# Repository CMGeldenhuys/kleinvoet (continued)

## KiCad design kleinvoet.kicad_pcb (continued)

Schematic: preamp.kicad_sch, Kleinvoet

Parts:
C1601: 18n; C_0805_2012Metric; MPN GRM21B5C1H183JA01K
C1602: PH/DNP; R_0402_1005Metric; not fitted
C1603, C1604: 2.7n; C_0402_1005Metric; MPN GRM1555C1H272GE01D
C1605: 1u; C_0402_1005Metric; MPN C0402C105K9PACTU
C1606, C1607: 220p; C_0402_1005Metric; MPN GRT1555C1H221FA02D
CB1601, CB1602: 100n; C_0402_1005Metric; MPN C0402C104K8PACTU
R1601, R1602: 270; R_0402_1005Metric; MPN RT0402FRE07270RL
R1603, R1604: 330E; R_0402_1005Metric; MPN RT0402FRE07330RL
R1605, R1606: 1k; R_0402_1005Metric; MPN RT0402FRE071KL
R1607, R1608: 15E; R_0402_1005Metric; MPN RT0402FRE0715RL
U1701: THS4551xRGT; VQFN-16-1EP_3x3mm_P0.5mm_EP1.68x1.68mm_ThermalVias; MPN THS4551IRGTR

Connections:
+1V8: CB1602.1, R1601.2, U1701.9 (VOCM); also elsewhere on the board
+3.3V_SENSOR: C1605.2, CB1601.1, U1701.5 (VS+), U1701.6 (VS+), U1701.7 (VS+), U1701.8 (VS+), U1701.12 (~PD); also elsewhere on the board
/Sensor_board/Preamplifier/FB: C1603.1, U1701.4 (FB+)
/Sensor_board/Preamplifier/FDA_IN: C1602.2, C1604.2, R1604.1, U1701.2 (IN+)
/Sensor_board/Preamplifier/FDA_~IN: C1602.1, C1603.2, R1603.1, U1701.3 (IN-)
/Sensor_board/Preamplifier/OUT: R1607.2, U1701.10 (OUT+)
/Sensor_board/Preamplifier/SIG_N: R1606.1, R1608.1; also elsewhere on the board
/Sensor_board/Preamplifier/SIG_P: R1605.1, R1607.1; also elsewhere on the board
/Sensor_board/Preamplifier/~FB: C1604.1, U1701.1 (FB-)
/Sensor_board/Preamplifier/~OUT: R1608.2, U1701.11 (OUT-)
/Sensor_board/SUM_OUT_P: R1602.2; also elsewhere on the board
GND_SENSOR: C1605.1, C1606.1, C1607.1, CB1601.2, CB1602.2, U1701.13 (VS-), U1701.14 (VS-), U1701.15 (VS-), U1701.16 (VS-), U1701.17 (EP); also elsewhere on the board
unnamed: C1601.1, C1606.2, R1601.1, R1603.2, R1605.2
unnamed: C1601.2, C1607.2, R1602.1, R1604.2, R1606.2

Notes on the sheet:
See sheet "/ADC_Interface/ADC_AA_1" for more information.
CONNECTED INTERNALLY

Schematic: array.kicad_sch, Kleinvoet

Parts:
C1401, C1402, C1501, C1503, C1505, C1506, C1507, C1508: 1u; C_0402_1005Metric; MPN C0402C105K9PACTU
CB1401, CB1402, CB1403, CB1404, CB1405, CB1406, CB1407, CB1408: 100n; C_0402_1005Metric; MPN C0402C104K8PACTU
MK1401, MK1402, MK1403, MK1404, MK1405, MK1406, MK1407, MK1408: MIC_ICS_40300; MEMS_Mic_ICS-40300; MPN ICS-40300

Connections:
+1V8: C1401.1, C1402.1, C1501.1, C1503.1, C1505.1, C1506.1, C1507.1, C1508.1, CB1401.1, CB1402.1, CB1403.1, CB1404.1, CB1405.1, CB1406.1, CB1407.1, CB1408.1, MK1401.5 (VDD), MK1402.5 (VDD), MK1403.5 (VDD), MK1404.5 (VDD), MK1405.5 (VDD), MK1406.5 (VDD), MK1407.5 (VDD), MK1408.5 (VDD); also elsewhere on the board
/Sensor_board/Buffer/IN0: MK1404.1 (OUTPUT); also elsewhere on the board
/Sensor_board/Buffer/IN1: MK1406.1 (OUTPUT); also elsewhere on the board
/Sensor_board/Buffer/IN2: MK1402.1 (OUTPUT); also elsewhere on the board
/Sensor_board/Buffer/IN3: MK1408.1 (OUTPUT); also elsewhere on the board
/Sensor_board/Buffer/IN4: MK1403.1 (OUTPUT); also elsewhere on the board
/Sensor_board/Buffer/IN5: MK1405.1 (OUTPUT); also elsewhere on the board
/Sensor_board/Buffer/IN6: MK1401.1 (OUTPUT); also elsewhere on the board
/Sensor_board/Buffer/IN7: MK1407.1 (OUTPUT); also elsewhere on the board
GND_SENSOR: C1401.2, C1402.2, C1501.2, C1503.2, C1505.2, C1506.2, C1507.2, C1508.2, CB1401.2, CB1402.2, CB1403.2, CB1404.2, CB1405.2, CB1406.2, CB1407.2, CB1408.2, MK1401.2 (GND), MK1401.3 (GND), MK1401.4 (GND), MK1401.6 (GND), MK1402.2 (GND), MK1402.3 (GND), MK1402.4 (GND), MK1402.6 (GND), MK1403.2 (GND), MK1403.3 (GND), MK1403.4 (GND), MK1403.6 (GND), MK1404.2 (GND), MK1404.3 (GND), MK1404.4 (GND), MK1404.6 (GND), MK1405.2 (GND), MK1405.3 (GND), MK1405.4 (GND), MK1405.6 (GND), MK1406.2 (GND), MK1406.3 (GND), MK1406.4 (GND), MK1406.6 (GND), MK1407.2 (GND), MK1407.3 (GND), MK1407.4 (GND), MK1407.6 (GND), MK1408.2 (GND), MK1408.3 (GND), MK1408.4 (GND), MK1408.6 (GND); also elsewhere on the board

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
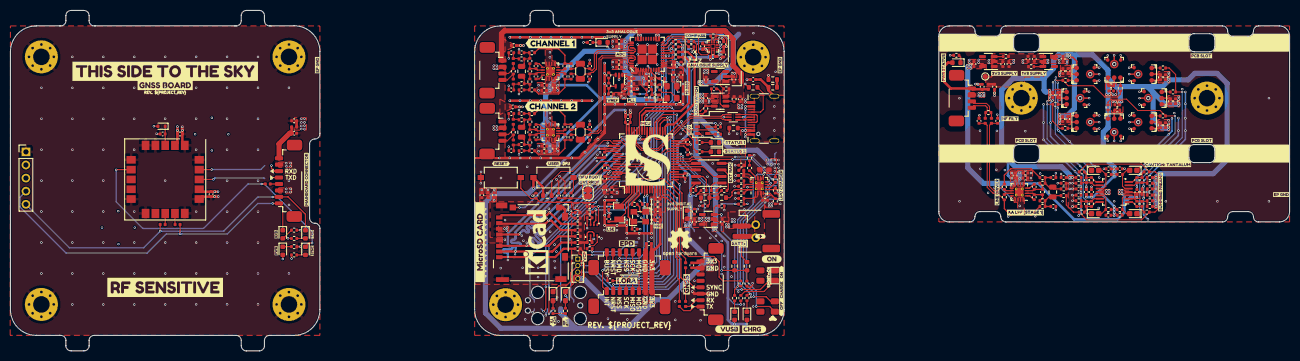
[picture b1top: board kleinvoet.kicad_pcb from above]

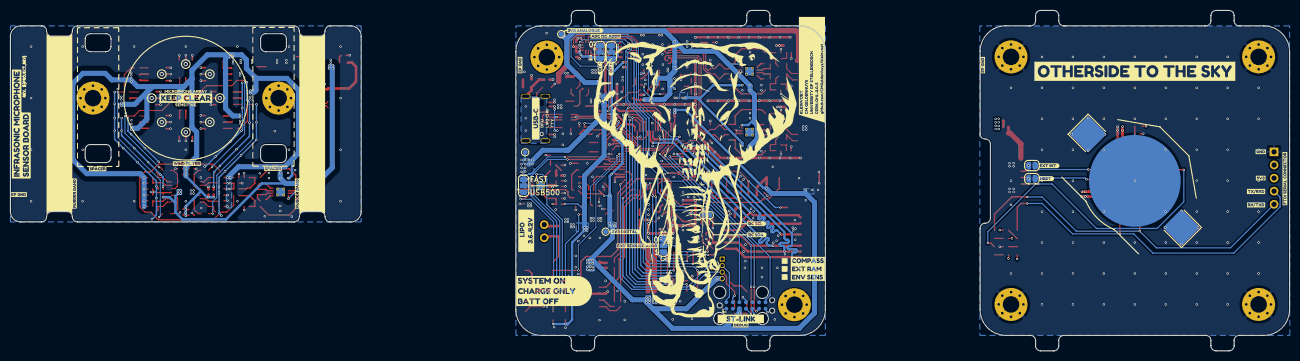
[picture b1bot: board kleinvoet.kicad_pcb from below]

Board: 4 copper layers, 248.0 x 66.0 mm, 500 parts (50 on the bottom side), 219 nets.

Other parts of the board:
303: Tab
B1, B2, B3: Board
T103, T104, T105, T106, T107, T109, T201, T203, T205, T206, T208, T209, T306, T307, T309, T311: Tab
kibuzzard-64FAE4D6: G***; kibuzzard-64FAE4D6
kibuzzard-64FAE5CE: G***; kibuzzard-64FAE5CE
kibuzzard-64FAE5F7: G***; kibuzzard-64FAE5F7
kibuzzard-64FAE496: G***; kibuzzard-64FAE496
kibuzzard-64FAEA81: G***; kibuzzard-64FAEA81
kibuzzard-64FAEAB3: G***; kibuzzard-64FAEAB3
kibuzzard-644FCAF5: G***; kibuzzard-644FCAF5
kibuzzard-644FCBD8: G***; kibuzzard-644FCBD8
kibuzzard-644FCBE4: G***; kibuzzard-644FCBE4
kibuzzard-644FCC8B: G***; kibuzzard-644FCC8B
kibuzzard-644FCC84: G***; kibuzzard-644FCC84
kibuzzard-644FCD41: G***; kibuzzard-644FCD41
kibuzzard-644FCD80: G***; kibuzzard-644FCD80
kibuzzard-644FCF30: G***; kibuzzard-644FCF30
kibuzzard-644FCFAB: G***; kibuzzard-644FCFAB
kibuzzard-644FD0BF: G***; kibuzzard-644FD0BF
kibuzzard-644FD0EC: G***; kibuzzard-644FD0EC
kibuzzard-644FD1C9: G***; kibuzzard-644FD1C9
kibuzzard-644FD1E4: G***; kibuzzard-644FD1E4
kibuzzard-644FD2E5: G***; kibuzzard-644FD2E5
kibuzzard-644FD9A3: G***; kibuzzard-644FD9A3
kibuzzard-644FD9EF: G***; kibuzzard-644FD9EF
kibuzzard-644FD32B: G***; kibuzzard-644FD32B
kibuzzard-644FD84A: G***; kibuzzard-644FD84A
kibuzzard-644FD97C: G***; kibuzzard-644FD97C
kibuzzard-644FD164: G***; kibuzzard-644FD164
kibuzzard-644FD811: G***; kibuzzard-644FD811
kibuzzard-644FD964: G***; kibuzzard-644FD964
kibuzzard-644FDA17: G***; kibuzzard-644FDA17
kibuzzard-644FDE8C: G***; kibuzzard-644FDE8C
kibuzzard-644FDEA0: G***; kibuzzard-644FDEA0
kibuzzard-644FDEAE: G***; kibuzzard-644FDEAE
kibuzzard-644FDEBE: G***; kibuzzard-644FDEBE
kibuzzard-644FDED0: G***; kibuzzard-644FDED0
kibuzzard-644FDEDF: G***; kibuzzard-644FDEDF
kibuzzard-644FDEEE: G***; kibuzzard-644FDEEE
kibuzzard-644FDF3B: G***; kibuzzard-644FDF3B
kibuzzard-644FDF29: G***; kibuzzard-644FDF29
kibuzzard-644FDF72: G***; kibuzzard-644FDF72
kibuzzard-644FDF97: G***; kibuzzard-644FDF97
kibuzzard-644FDFE0: G***; kibuzzard-644FDFE0
kibuzzard-644FDFE9: G***; kibuzzard-644FDFE9
kibuzzard-644FE0B0: G***; kibuzzard-644FE0B0
kibuzzard-644FE0C7: G***; kibuzzard-644FE0C7
kibuzzard-644FE0D3: G***; kibuzzard-644FE0D3
kibuzzard-644FE0E6: G***; kibuzzard-644FE0E6
kibuzzard-644FE0FE: G***; kibuzzard-644FE0FE
kibuzzard-644FE022: G***; kibuzzard-644FE022
kibuzzard-644FE057: G***; kibuzzard-644FE057
kibuzzard-644FEC52: G***; kibuzzard-644FEC52
kibuzzard-644FEC78: G***; kibuzzard-644FEC78
kibuzzard-693A62A4: G***; kibuzzard-693A62A4
kibuzzard-6937DD7F: G***; kibuzzard-6937DD7F
kibuzzard-6937DDBE: G***; kibuzzard-6937DDBE
kibuzzard-6937DDCD: G***; kibuzzard-6937DDCD
kibuzzard-6937DDE0: G***; kibuzzard-6937DDE0
kibuzzard-6937E0C6: G***; kibuzzard-6937E0C6
kibuzzard-6937E02E: G***; kibuzzard-6937E02E
kibuzzard-6937E9BB: G***; kibuzzard-6937E9BB
kibuzzard-6937E996: G***; kibuzzard-6937E996
kibuzzard-6937EA9A: G***; kibuzzard-6937EA9A
kibuzzard-64588AF5: G***; kibuzzard-64588AF5
kibuzzard-64588B83, kibuzzard-64588B83#2: G***; kibuzzard-64588B83
kibuzzard-64588C0F: G***; kibuzzard-64588C0F
kibuzzard-64588C44: G***; kibuzzard-64588C44
kibuzzard-64588CA5: G***; kibuzzard-64588CA5
kibuzzard-64588D6D: G***; kibuzzard-64588D6D
kibuzzard-64588D28, kibuzzard-64588D28#2, kibuzzard-64588D28#3: G***; kibuzzard-64588D28
kibuzzard-64588D84: G***; kibuzzard-64588D84
kibuzzard-64588F88, kibuzzard-64588F88#2: G***; kibuzzard-64588F88
kibuzzard-64588FFA: G***; kibuzzard-64588FFA
kibuzzard-64589A68: G***; kibuzzard-64589A68
kibuzzard-645890C3: G***; kibuzzard-645890C3
kibuzzard-645890EE: G***; kibuzzard-645890EE
kibuzzard-645891C0: G***; kibuzzard-645891C0
kibuzzard-645891F3: G***; kibuzzard-645891F3
kibuzzard-645892E6, kibuzzard-645892E6#2, kibuzzard-645892E6#3, kibuzzard-645892E6#4, kibuzzard-645892E6#5, kibuzzard-645892E6#6: G***; kibuzzard-645892E6
kibuzzard-6458903B: G***; kibuzzard-6458903B
kibuzzard-6458905C: G***; kibuzzard-6458905C
kibuzzard-6458907D: G***; kibuzzard-6458907D
kibuzzard-6458908B: G***; kibuzzard-6458908B
kibuzzard-6458936C: G***; kibuzzard-6458936C
kibuzzard-6458938C: G***; kibuzzard-6458938C
kibuzzard-64589097: G***; kibuzzard-64589097
kibuzzard-64589363: G***; kibuzzard-64589363

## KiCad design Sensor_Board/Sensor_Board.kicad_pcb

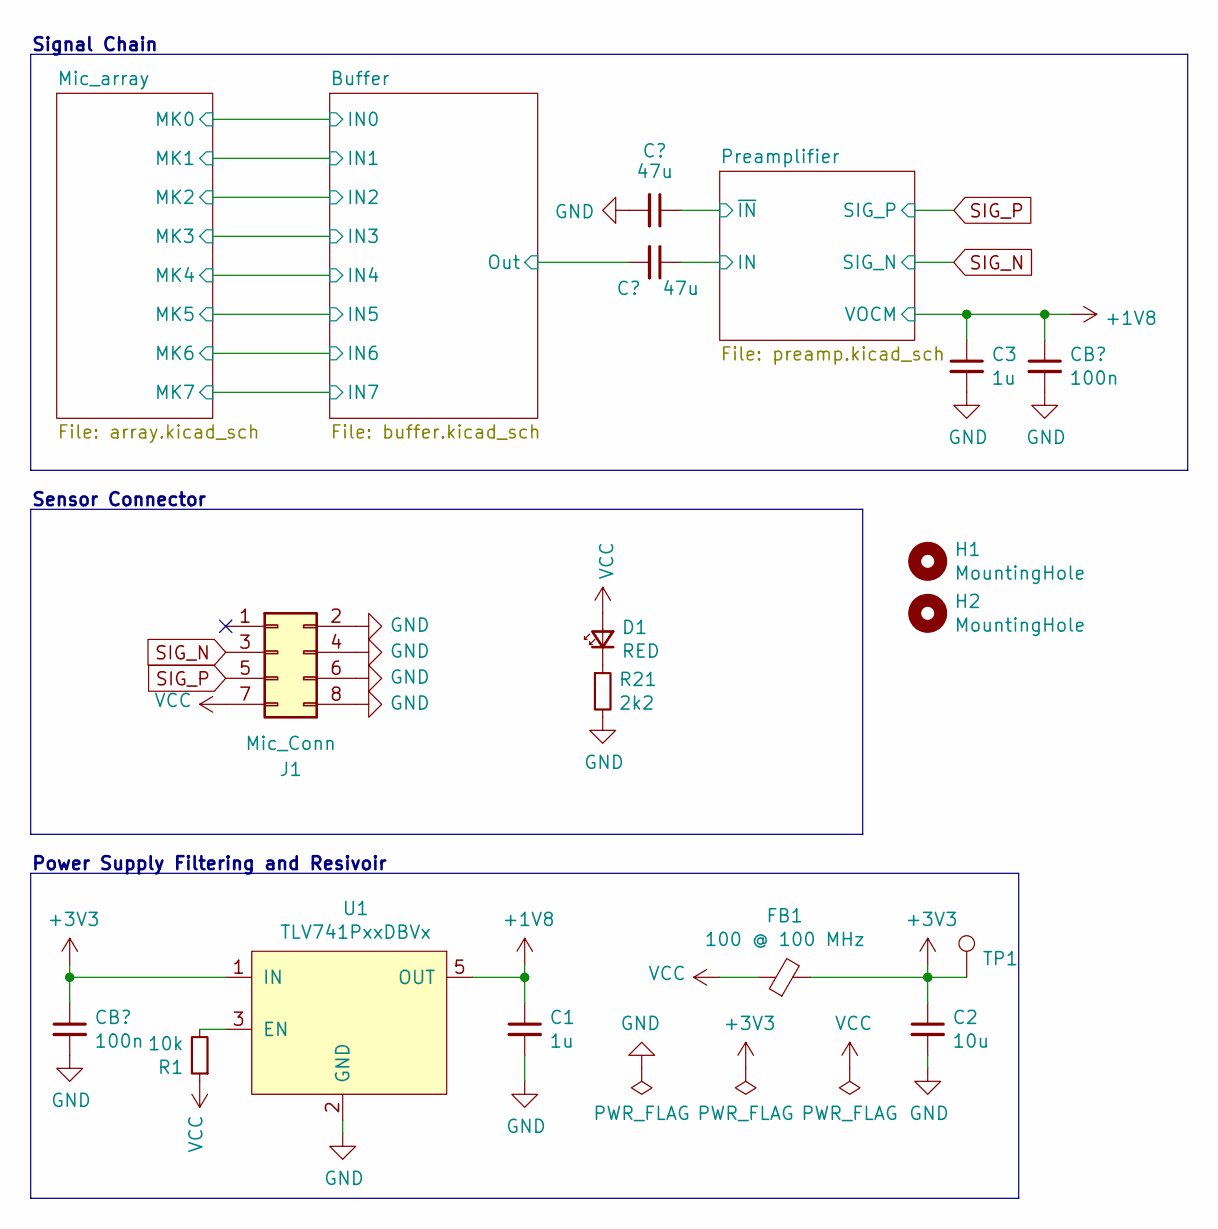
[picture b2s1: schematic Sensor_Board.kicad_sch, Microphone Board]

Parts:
C1, C3: 1u; C_0603_1608Metric_Pad1.08x0.95mm_HandSolder; MPN C0603C105K8RACTU
C2: 10u; C_0805_2012Metric_Pad1.18x1.45mm_HandSolder; MPN C0805C106K9PACTU
C10, C11: 47u; C_1206_3216Metric_Pad1.33x1.80mm_HandSolder; MPN GRM31CR60J107KE39K
CB1, CB3: 100n; C_0603_1608Metric_Pad1.08x0.95mm_HandSolder; MPN C0603C104M5RACTU
D1: RED; LED_0603_1608Metric_Pad1.05x0.95mm_HandSolder; MPN SML-D12U8WT86C
FB1: 100 @ 100 MHz; L_0603_1608Metric_Pad1.05x0.95mm_HandSolder; MPN BLM18EG101TZ1D
H1, H2: MountingHole; MountingHole_3.2mm_M3_Pad_Via
J1: Mic_Conn; TE_7-215079-8; MPN 7-215079-8, 7-215083-8
R1: 10k; R_0603_1608Metric_Pad0.98x0.95mm_HandSolder; MPN RC0603JR-0710KL
R21: 2k2; R_0603_1608Metric_Pad0.98x0.95mm_HandSolder; MPN ERJ-3EKF2201V
TP1: TestPoint; TestPoint_Pad_D1.0mm; MPN ICS-40300
U1: TLV741PxxDBVx; SOT-23-5; MPN TLV74118PDBVR

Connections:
+1V8: C1.1, C3.1, CB3.1, U1.5 (OUT); also elsewhere on the board
+3V3: C2.1, CB1.1, FB1.2, TP1.1, U1.1 (IN); also elsewhere on the board
/Buffer/Out: C11.2; also elsewhere on the board
/Preamplifier/IN: C11.1; also elsewhere on the board
/Preamplifier/~IN: C10.1; also elsewhere on the board
GND: C1.2, C2.2, C3.2, C10.2, CB1.2, CB3.2, J1.2, J1.4, J1.6, J1.8, R21.2, U1.2 (GND); also elsewhere on the board
unnamed: D1.1 (K), R21.1
unnamed: R1.2, U1.3 (EN)
SIG_N: J1.3; also elsewhere on the board
SIG_P: J1.5; also elsewhere on the board
VCC: D1.2 (A), FB1.1, J1.7, R1.1

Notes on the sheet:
Power Supply Filtering and Resivoir
Signal Chain
Sensor Connector

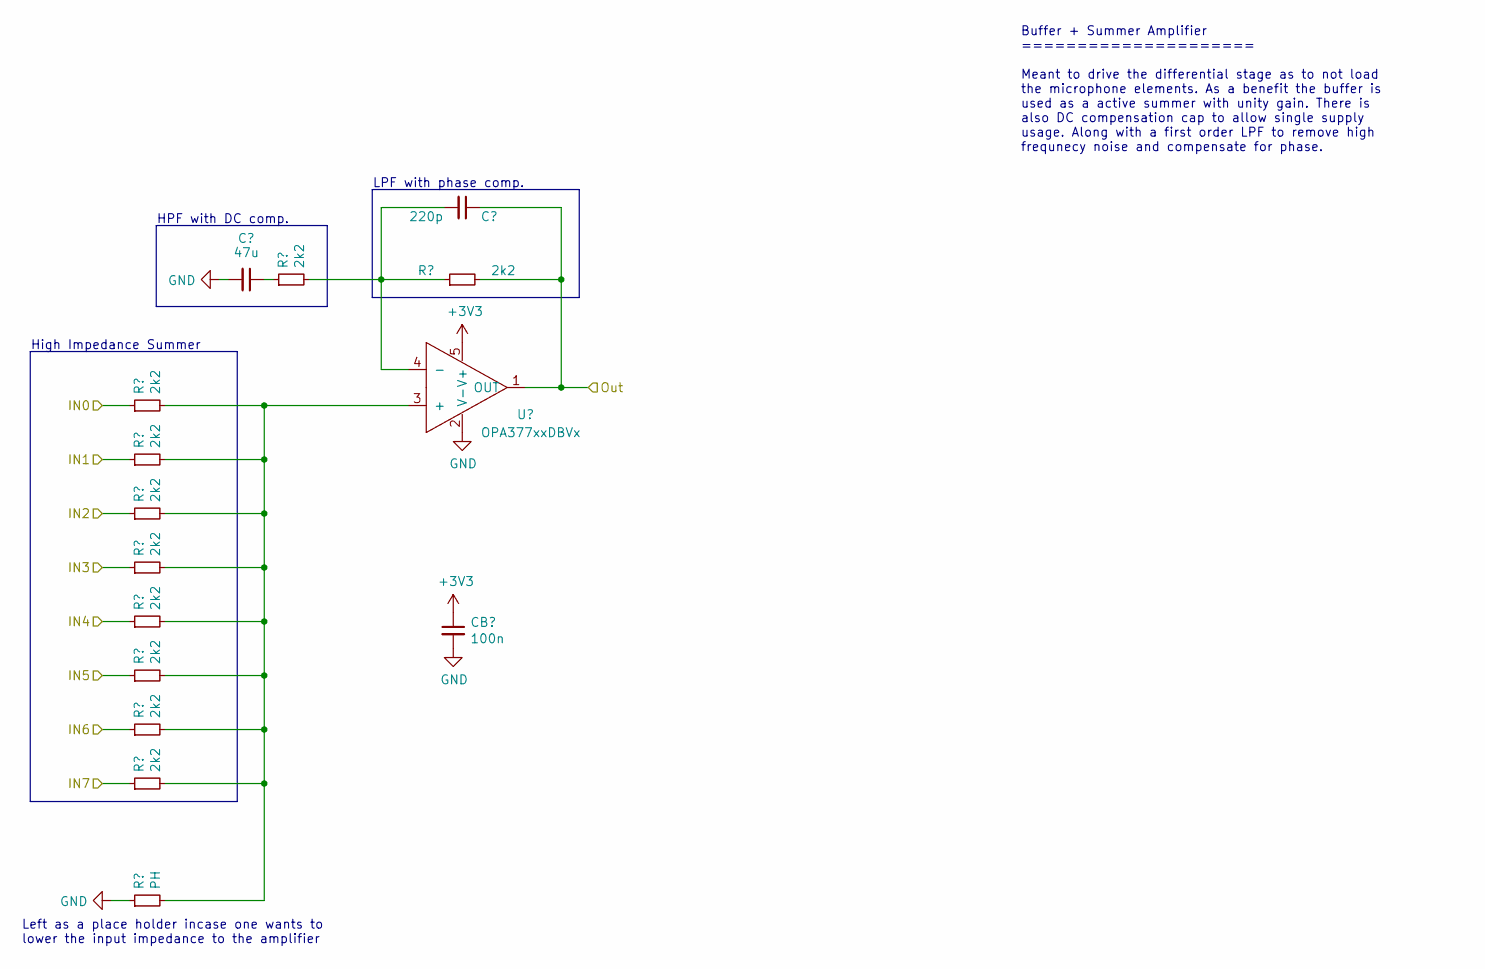
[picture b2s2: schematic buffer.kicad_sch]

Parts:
C4: 47u; C_1206_3216Metric_Pad1.33x1.80mm_HandSolder; MPN GRM31CR60J107KE39K
C5: 220p; C_0603_1608Metric_Pad1.08x0.95mm_HandSolder; MPN C0603C221J5GACTU
CB4: 100n; C_0603_1608Metric_Pad1.08x0.95mm_HandSolder; MPN C0603C104M5RACTU
R2, R3, R4, R5, R6, R7, R8, R9, R11, R12: 2k2; R_0603_1608Metric_Pad0.98x0.95mm_HandSolder; MPN ERJ-3EKF2201V
R10: PH; R_0603_1608Metric_Pad0.98x0.95mm_HandSolder
U2: OPA377xxDBVx; SOT-23-5; MPN OPA377AIDBVR

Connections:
+3V3: CB4.1, U2.5 (V+); also elsewhere on the board
/Buffer/IN0: R2.1; also elsewhere on the board
/Buffer/IN1: R3.1; also elsewhere on the board
/Buffer/IN2: R4.1; also elsewhere on the board
/Buffer/IN3: R5.1; also elsewhere on the board
/Buffer/IN4: R6.1; also elsewhere on the board
/Buffer/IN5: R7.1; also elsewhere on the board
/Buffer/IN6: R8.1; also elsewhere on the board
/Buffer/IN7: R9.1; also elsewhere on the board
/Buffer/Out: C5.1, R12.2, U2.1 (OUT); also elsewhere on the board
GND: C4.2, CB4.2, R10.1, U2.2 (V-); also elsewhere on the board
unnamed: C4.1, R11.1
unnamed: C5.2, R11.2, R12.1, U2.4 (-)
unnamed: R2.2, R3.2, R4.2, R5.2, R6.2, R7.2, R8.2, R9.2, R10.2, U2.3 (+)

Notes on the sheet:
Buffer + Summer Amplifier ===================== Meant to drive the differential stage as to not load the microphone elements. As a benefit the buffer is used as a active summer with unity gain. There is also DC compensation cap to allow single supply usage. Along with a first order LPF to remove hi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
HPF with DC comp.
High Impedance Summer
LPF with phase comp.
Left as a place holder incase one wants to lower the input impedance to the amplifier

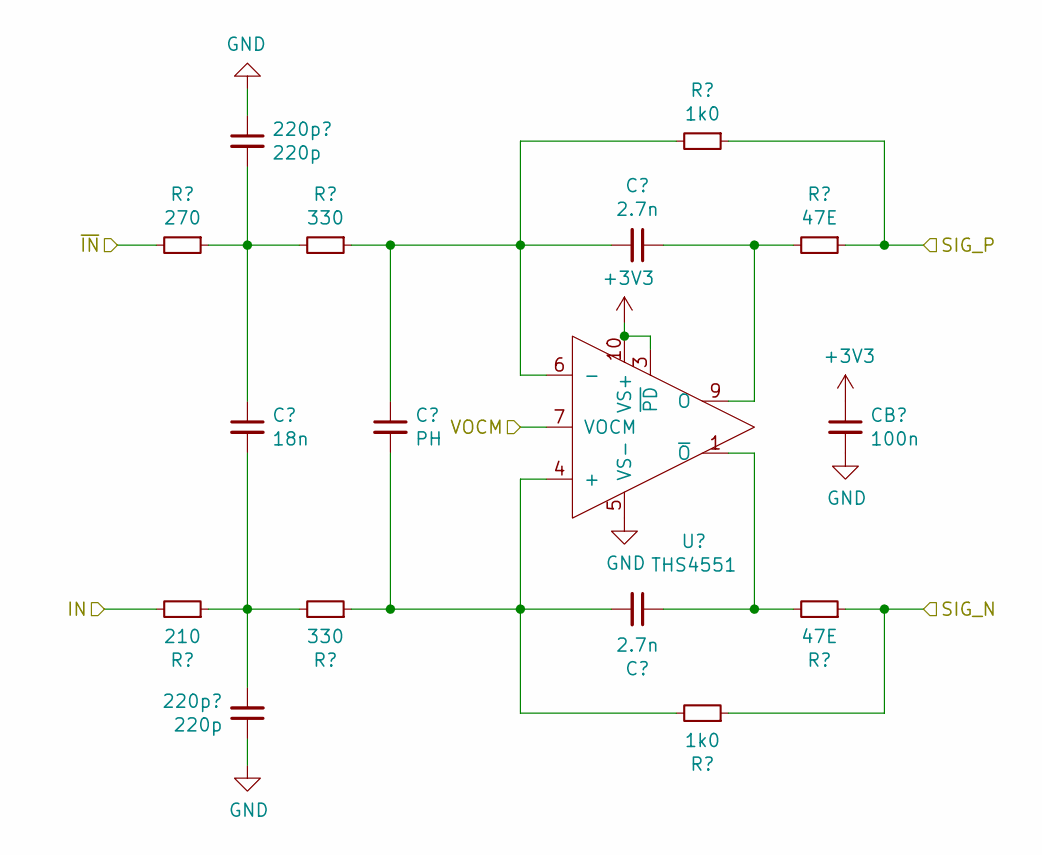
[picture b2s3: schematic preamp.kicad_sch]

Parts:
C6: 18n; C_0603_1608Metric_Pad1.08x0.95mm_HandSolder; MPN CC0603JRX7R8BB183
C7: PH; R_0603_1608Metric_Pad0.98x0.95mm_HandSolder
C8, C9: 2.7n; C_0603_1608Metric_Pad1.08x0.95mm_HandSolder; MPN CC0603JRX7R9BB272
C12, C13: 220p; C_0603_1608Metric_Pad1.08x0.95mm_HandSolder; MPN C0603C221J5GACTU
CB5: 100n; C_0603_1608Metric_Pad1.08x0.95mm_HandSolder; MPN C0603C104M5RACTU
R13: 270; R_0603_1608Metric_Pad0.98x0.95mm_HandSolder; MPN ERJ-3EKF2700V
R14: 210; R_0603_1608Metric_Pad0.98x0.95mm_HandSolder; MPN ERJ-3EKF2100V
R15, R16: 330; R_0603_1608Metric_Pad0.98x0.95mm_HandSolder; MPN ERJ-3EKF3300V
R17, R18: 1k0; R_0603_1608Metric_Pad0.98x0.95mm_HandSolder; MPN ERJ-3EKF1001V
R19, R20: 47E; R_0603_1608Metric_Pad0.98x0.95mm_HandSolder; MPN ERJ-3EKF47R0V
U3: THS4551; WQFN-10_RUN; MPN THS4551IRUNR

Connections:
+1V8: U3.7 (VOCM); also elsewhere on the board
+3V3: CB5.1, U3.3 (~PD), U3.10 (VS+); also elsewhere on the board
/Preamplifier/IN: R14.2; also elsewhere on the board
/Preamplifier/~IN: R13.2; also elsewhere on the board
GND: C12.1, C13.1, CB5.2, U3.5 (VS-); also elsewhere on the board
unnamed: C7.1, C8.2, R15.1, R17.2, U3.6 (-)
unnamed: C7.2, C9.2, R16.1, R18.2, U3.4 (+)
unnamed: C8.1, R19.2, U3.9 (O)
unnamed: C9.1, R20.2, U3.1 (~O)
unnamed: C6.1, C12.2, R13.1, R15.2
unnamed: C6.2, C13.2, R14.1, R16.2
SIG_N: R18.1, R20.1; also elsewhere on the board
SIG_P: R17.1, R19.1; also elsewhere on the board

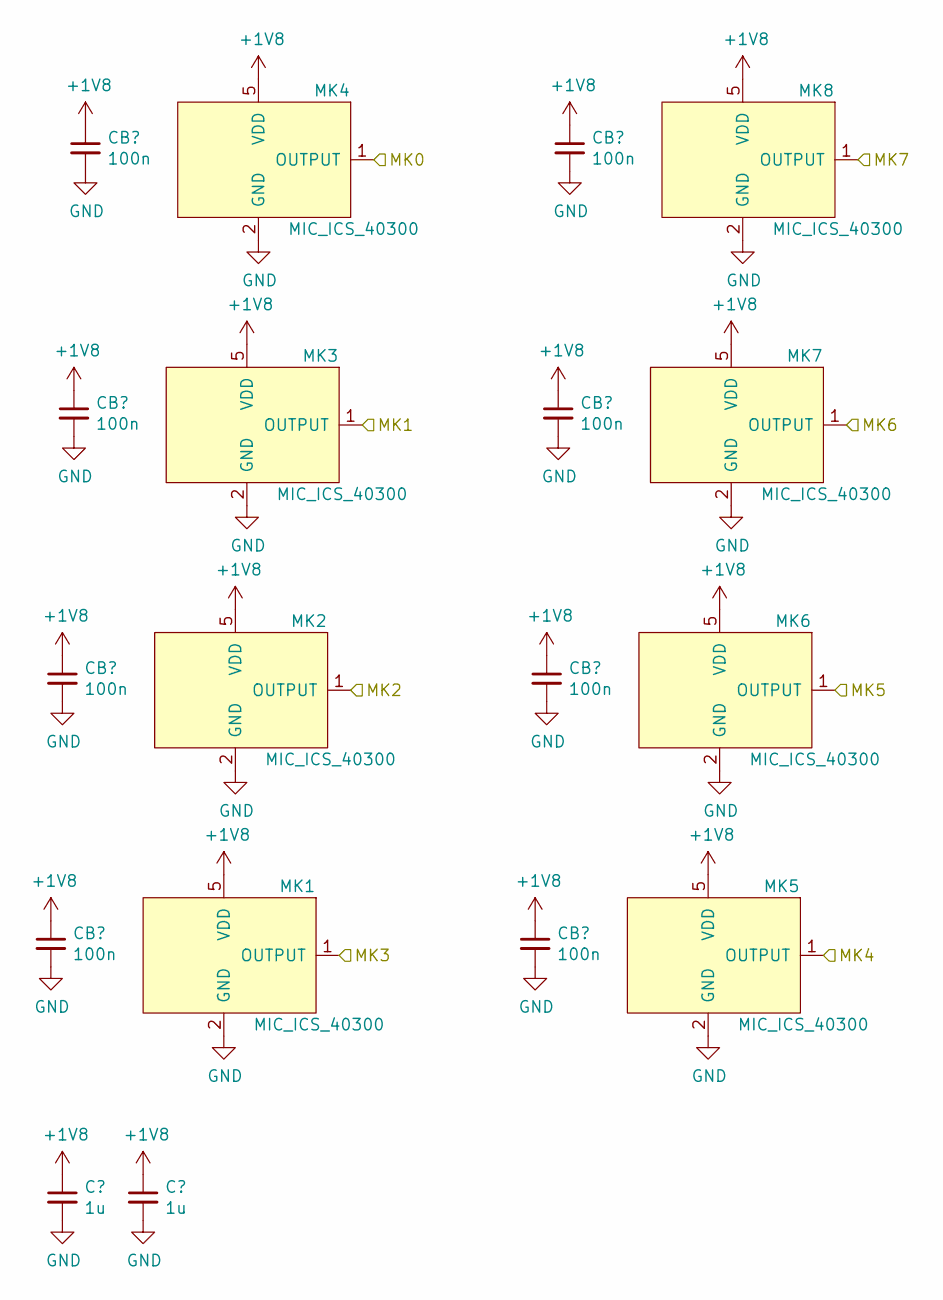
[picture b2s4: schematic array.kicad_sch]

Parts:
C14, C15: 1u; C_0603_1608Metric_Pad1.08x0.95mm_HandSolder; MPN C0603C105K8RACTU
CB6, CB7, CB8, CB9, CB10, CB11, CB12, CB13: 100n; C_0603_1608Metric_Pad1.08x0.95mm_HandSolder; MPN C0603C104M5RACTU
MK1, MK2, MK3, MK4, MK5, MK6, MK7, MK8: MIC_ICS_40300; MEMS_Mic_ICS-40300; MPN ICS-40300

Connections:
+1V8: C14.1, C15.1, CB6.1, CB7.1, CB8.1, CB9.1, CB10.1, CB11.1, CB12.1, CB13.1, MK1.5 (VDD), MK2.5 (VDD), MK3.5 (VDD), MK4.5 (VDD), MK5.5 (VDD), MK6.5 (VDD), MK7.5 (VDD), MK8.5 (VDD); also elsewhere on the board
/Buffer/IN0: MK4.1 (OUTPUT); also elsewhere on the board
/Buffer/IN1: MK3.1 (OUTPUT); also elsewhere on the board
/Buffer/IN2: MK2.1 (OUTPUT); also elsewhere on the board
/Buffer/IN3: MK1.1 (OUTPUT); also elsewhere on the board
/Buffer/IN4: MK5.1 (OUTPUT); also elsewhere on the board
/Buffer/IN5: MK6.1 (OUTPUT); also elsewhere on the board
/Buffer/IN6: MK7.1 (OUTPUT); also elsewhere on the board
/Buffer/IN7: MK8.1 (OUTPUT); also elsewhere on the board
GND: C14.2, C15.2, CB6.2, CB7.2, CB8.2, CB9.2, CB10.2, CB11.2, CB12.2, CB13.2, MK1.2 (GND), MK1.3 (GND), MK1.4 (GND), MK1.6 (GND), MK2.2 (GND), MK2.3 (GND), MK2.4 (GND), MK2.6 (GND), MK3.2 (GND), MK3.3 (GND), MK3.4 (GND), MK3.6 (GND), MK4.2 (GND), MK4.3 (GND), MK4.4 (GND), MK4.6 (GND), MK5.2 (GND), MK5.3 (GND), MK5.4 (GND), MK5.6 (GND), MK6.2 (GND), MK6.3 (GND), MK6.4 (GND), MK6.6 (GND), MK7.2 (GND), MK7.3 (GND), MK7.4 (GND), MK7.6 (GND), MK8.2 (GND), MK8.3 (GND), MK8.4 (GND), MK8.6 (GND); also elsewhere on the board

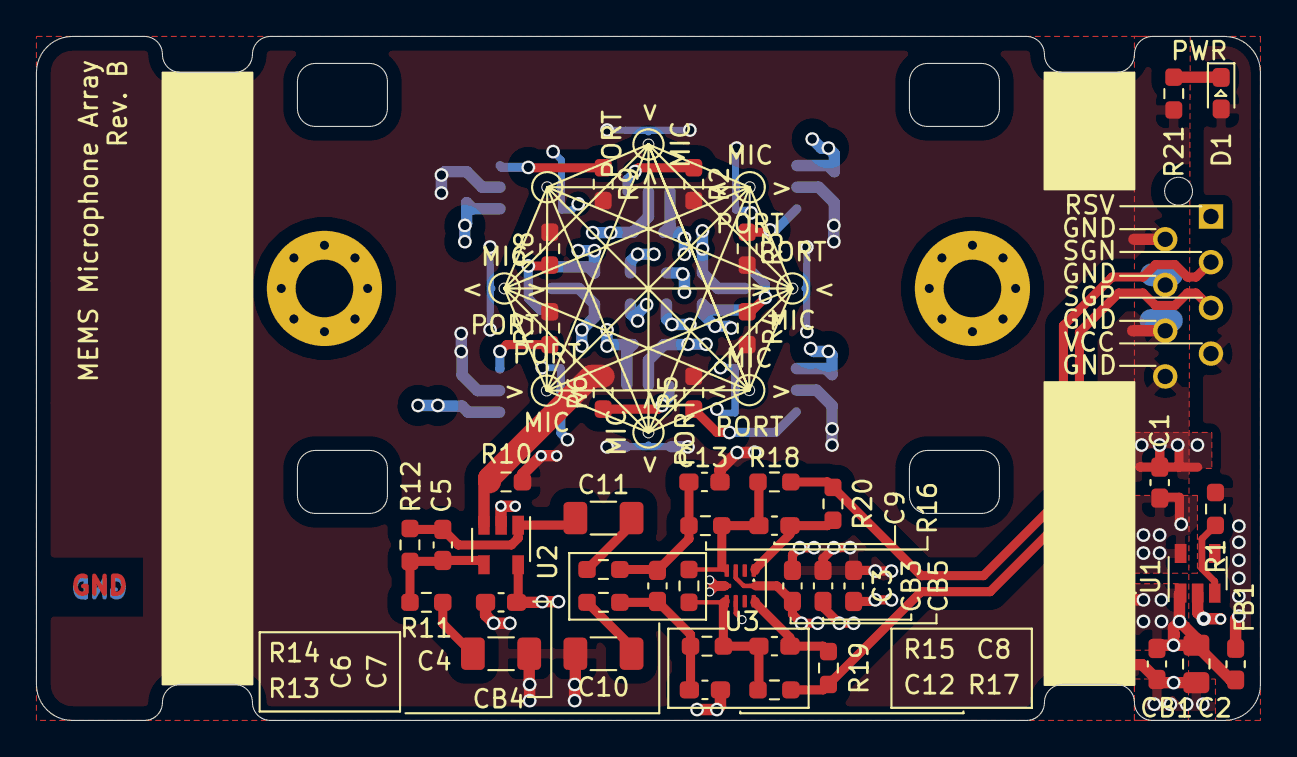
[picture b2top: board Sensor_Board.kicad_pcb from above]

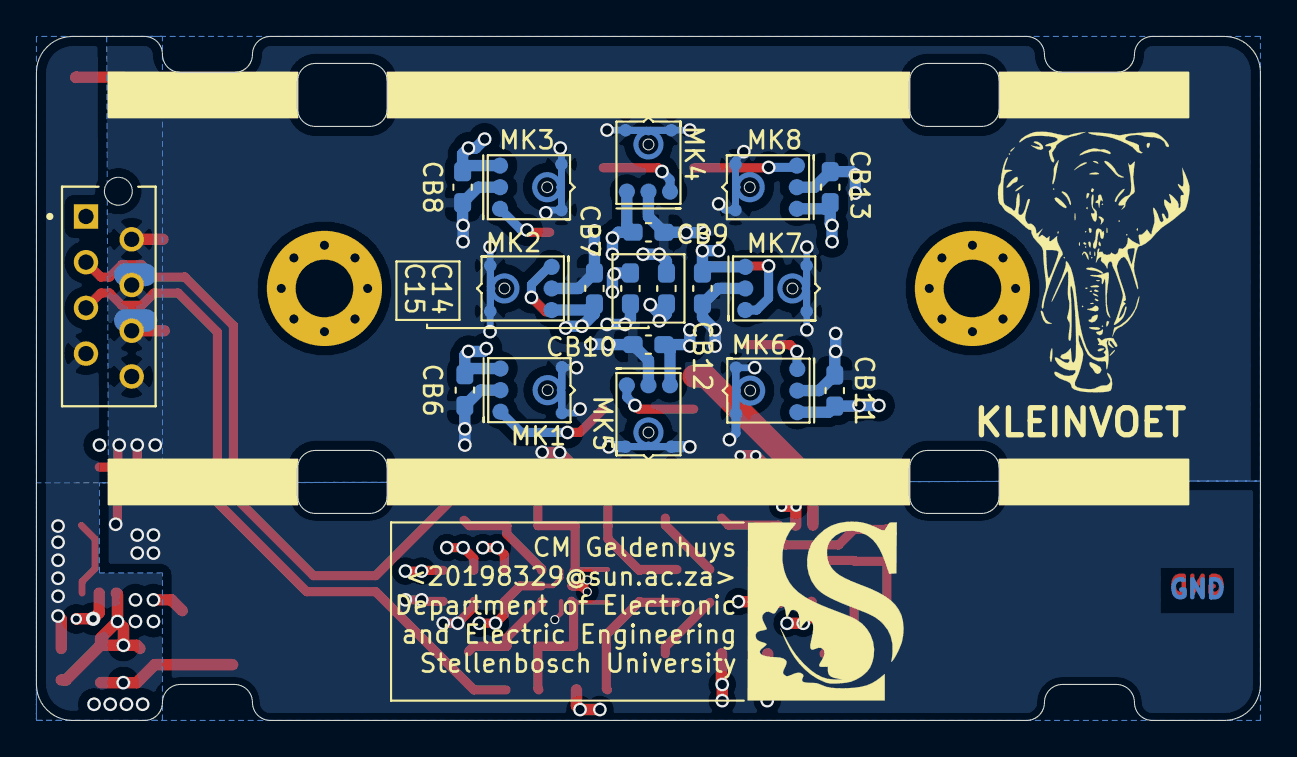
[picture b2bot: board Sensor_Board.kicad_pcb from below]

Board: 4 copper layers, 68.0 x 38.0 mm, 65 parts (19 on the bottom side), 28 nets.

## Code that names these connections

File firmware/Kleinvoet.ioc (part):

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Mcu.Name=STM32F446R(C-E)Tx
Mcu.Package=LQFP64
Mcu.UserName=STM32F446RCTx
PA0-WKUP.GPIOParameters=GPIO_Label
PA0-WKUP.GPIO_Label=GPS_TX
PA0-WKUP.Mode=Asynchronous
PA0-WKUP.Signal=UART4_TX
PA1.GPIOParameters=GPIO_Label
PA1.GPIO_Label=GPS_RX
PA1.Mode=Asynchronous
PA1.Signal=UART4_RX
PA11.Mode=Device_Only
PA11.Signal=USB_OTG_FS_DM
PA12.Mode=Device_Only
PA12.Signal=USB_OTG_FS_DP
PA13.Mode=Trace_Asynchronous_SW
PA13.Signal=SYS_JTMS-SWDIO
PA14.Mode=Trace_Asynchronous_SW
PA14.Signal=SYS_JTCK-SWCLK
PA15.GPIOParameters=GPIO_Label
PA15.GPIO_Label=LED_STATUS
PA15.Signal=GPIO_Output
PA2.GPIOParameters=GPIO_Label
PA2.GPIO_Label=VCP_TX
PA2.Mode=Asynchronous
PA2.Signal=USART2_TX
PA3.GPIOParameters=GPIO_Label
PA3.GPIO_Label=VCP_RX
PA3.Mode=Asynchronous
PA3.Signal=USART2_RX
PA4.GPIOParameters=GPIO_Label
PA4.GPIO_Label=CAL_SIG
PA4.Signal=COMP_DAC1_group
PA5.GPIOParameters=GPIO_Label
PA5.GPIO_Label=FLASH_SCK
PA5.Mode=Full_Duplex_Master
PA5.Signal=SPI1_SCK
PA6.GPIOParameters=GPIO_Label
PA6.GPIO_Label=FLASH_MISO
PA6.Mode=Full_Duplex_Master
PA6.Signal=SPI1_MISO
PA7.GPIOParameters=GPIO_Label
PA7.GPIO_Label=FLASH_MOSI
PA7.Mode=Full_Duplex_Master
PA7.Signal=SPI1_MOSI
PA8.GPIOParameters=GPIO_Label
PA8.GPIO_Label=SDIO_CD
PA8.Signal=GPIO_Input
PA9.GPIOParameters=GPIO_Label
PA9.GPIO_Label=SDIO_WP
PA9.Signal=GPIO_Input
PB0.GPIOParameters=GPIO_Label
PB0.GPIO_Label=GPS_nSAFEBOOT
PB0.Signal=GPIO_Output
PB1.GPIOParameters=GPIO_Label
PB1.GPIO_Label=V_MONITOR
PB1.Signal=ADCx_IN9
PB10.GPIOParameters=GPIO_Label
PB10.GPIO_Label=GPS_WAKE
PB10.Signal=GPIO_Output
PB12.GPIOParameters=GPIO_Label
PB12.GPIO_Label=ADC_nREADY
PB12.Signal=GPXTI12
PB13.GPIOParameters=GPIO_Label
PB13.GPIO_Label=ADC_SCK
PB13.Mode=Full_Duplex_Master
PB13.Signal=SPI2_SCK
PB14.GPIOParameters=GPIO_Label
PB14.GPIO_Label=ADC_MISO
PB14.Mode=Full_Duplex_Master
PB14.Signal=SPI2_MISO
PB15.GPIOParameters=GPIO_Label
PB15.GPIO_Label=ADC_MOSI
PB15.Mode=Full_Duplex_Master
PB15.Signal=SPI2_MOSI
PB2.GPIOParameters=GPIO_Label
PB2.GPIO_Label=nUSER_BTN
PB2.Signal=GPIO_Input
PB3.Mode=Trace_Asynchronous_SW
PB3.Signal=SYS_JTDO-SWO
PB8.GPIOParameters=GPIO_Label
PB8.GPIO_Label=USR_BTN
PB8.Signal=GPIO_Input
PC10.Mode=SD_4_bits_Wide_bus
PC10.Signal=SDIO_D2
PC11.Mode=SD_4_bits_Wide_bus
PC11.Signal=SDIO_D3
PC12.Mode=SD_4_bits_Wide_bus
PC12.Signal=SDIO_CK
PC13.GPIOParameters=GPIO_Label
PC13.GPIO_Label=RTC_CAL
PC13.Mode=Calibration_512Hz
PC13.Signal=RTC_AF1
PC14-OSC32_IN.GPIOParameters=GPIO_Label
PC14-OSC32_IN.GPIO_Label=LSE_IN
PC14-OSC32_IN.Mode=LSE-External-Oscillator
PC14-OSC32_IN.Signal=RCC_OSC32_IN
PC15-OSC32_OUT.GPIOParameters=GPIO_Label
PC15-OSC32_OUT.GPIO_Label=LSE_OUT
PC15-OSC32_OUT.Mode=LSE-External-Oscillator
PC15-OSC32_OUT.Signal=RCC_OSC32_OUT
PC4.GPIOParameters=GPIO_Label
PC4.GPIO_Label=CAL_EN
PC4.Signal=GPIO_Analog
PC5.GPIOParameters=GPIO_Label
PC5.GPIO_Label=SENSOR_EN
PC5.Signal=GPIO_Analog
PC6.GPIOParameters=GPIO_Label
PC6.GPIO_Label=ADC_nCS
PC6.Signal=GPIO_Output
PC7.GPIOParameters=GPIO_Label
PC7.GPIO_Label=ADC_CLK
PC7.Signal=GPIO_Analog
PC8.Mode=SD_4_bits_Wide_bus
PC8.Signal=SDIO_D0
PC9.Mode=SD_4_bits_Wide_bus
PC9.Signal=SDIO_D1
PD2.Mode=SD_4_bits_Wide_bus
PD2.Signal=SDIO_CMD
PH0-OSC_IN.GPIOParameters=GPIO_Label
PH0-OSC_IN.GPIO_Label=HSE_IN
PH0-OSC_IN.Mode=HSE-External-Oscillator
PH0-OSC_IN.Signal=RCC_OSC_IN
PH1-OSC_OUT.GPIOParameters=GPIO_Label
PH1-OSC_OUT.GPIO_Label=HSE_OUT
PH1-OSC_OUT.Mode=HSE-External-Oscillator
PH1-OSC_OUT.Signal=RCC_OSC_OUT
RCC.HSE_VALUE=12000000
board=custom

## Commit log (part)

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2023-03-07 (sch) update usr button to trigger boot0
2023-03-07 (footprint) add Tag Connect
2023-03-07 (repo) ignore auto saves
2023-03-07 (sch) add JTAG 5 pin
2023-03-07 (sch) split out GPS NRST
2023-03-07 (sch) add pull up and notes to ADC
2023-03-07 (sch) add new power path IC
2023-03-07 (sch) change termination resistor
2023-03-07 (bkup)
2023-03-07 (deps) update sensorboard to KiCad 7.0
2023-03-08 (libs) add amphenol footprint
2023-03-08 (hk) drop unused part fields
2023-03-08 (hk) add MPN to power switch
2023-03-08 (sch) add timepulse LED
2023-03-08 (sch) add new GNSS connector
2023-03-08 (sch) move out GNSS BATT
2023-03-08 (sch) new sensor connector interface
2023-03-08 (sch) add lora connector
2023-03-08 (sch) remap unimportantn pins
2023-03-09 (bkup) add new backups
2023-03-09 (bc) add sensorboard changes
2023-03-13 (sch) add battery charger override jumper
2023-03-13 (hk) resize comment box
2023-03-13 (sch) add new pin assigment
2023-03-13 big commit
2023-03-13 (deps) upgrade
2023-03-13 (hk) add backups
2023-03-14 Big commit for the day
2023-03-14 update libs
2023-03-15 (sch) change debug footprint
2023-03-15 (sch) add serial pin interface
2023-03-16 (spice) start on new design
2023-03-16 (sch) add hf comp
2023-03-16 (sch) checkpoint
2023-03-16 (sch) DC servo
2023-03-16 (sch) inv amp with DC servo
2023-03-16 (sch) finalise circuit
2023-03-16 (spice) add models to lib
2023-03-16 (repo) add backups
2023-03-20 (spice) finish DC servo with noise comp & effective cap
2023-03-20 (spice) add opamp models
2023-03-20 (spice) add diff output with offset correction
2023-03-20 (spice) final design
2023-03-21 (hk) save spice
2023-03-22 (bc) new summation preamp & seperate power net
2023-03-22 (script) add compute adc clk
2023-03-22 (bc) changes for the day
2023-03-22 (sch) relabel
2023-03-22 (sch) update sch from lib
2023-03-22 (drc) start processing DRCs
2023-03-24 (bc) finish up ERC
2023-03-24 (libs) fix 1.8v reg
2023-03-24 (hk) asign footprints
2023-03-24 (sch) fix exessive power filtering
2023-03-24 (sch) add net lables for GNSS
2023-03-24 (sch) change xtal C to 0402
2023-03-24 (pcb) start on rev c
2023-03-26 (repo) clean up README
2023-03-27 (repo) add sample recording
2023-03-27 (repo) clean up
2023-03-27 (sch) change passives to 0402
2023-03-27 (pcb) board setup for TRAX
2023-03-29 (hk) checkin backups
2023-03-29 (pcb) initial layout
2023-03-30 (sch) replace voltage ref with ADC ref + buf
2023-03-30 (libs) add TLV333
2023-03-30 (pcb) update ics40300 footprint
2023-03-31 (sch) change LDOs
2023-03-31 (sch) replace PWR SW with DP3T
2023-03-31 (pcb) update from sch
2023-03-31 (libs) add DP3T footprint
2023-03-31 (sch) add I2C pull ups
2023-03-31 (sch) plan env sensor, DNP
2023-03-31 (hk) update main sch
2023-04-03 (sch) change default charging & add PWR LEDs
2023-04-03 (sch) fix GNSS GND & pinout
2023-04-03 (pcb) GNSS board layout
2023-04-03 (libs) update footprints
2023-04-11 (docs) add pcb panel PDF files
2023-04-11 (docs) add pcb PDF files
2023-04-11 (docs) add PDF schematics
2023-04-11 (docs) update README with PCB layout and sch PDFs
2023-04-11 (wip) set up project netclasses
2023-04-11 (sch) fix BTN pull-up/down
2023-04-11 (sch) update annotations
2023-04-11 (sch) add PWR LED to BOM
2023-04-11 (pcb) work on rough layout
2023-04-11 (sch) add net labels
2023-04-12 (sch) remove pull-up R I2C for BME280
2023-04-12 (sch) annotate compass pins
2023-04-12 (sch) annotate env-sens pins
2023-04-12 (pcb) XTAL layout
2023-04-12 (pcb) hide all reference designators
2023-04-12 (proj) add MPN & MFR fields to all parts
2023-04-12 (pcb) update default traces & teardrops
2023-04-12 (sch) update project to use VAR REV
2023-04-12 (pcb) update silkscreen to use proj VAR
2023-04-12 (pcb) improve ADC driver layout
2023-04-12 (hk) checkin backups & conf
2023-04-12 (pcb) fix xtal perimeter
2023-04-12 (sch) remove stability comp ADC driver & annotate
2023-04-12 (sch) remove ADC driver input cap
    Originally introduced to help with stability. However was never utilised and
    not required by the design. Ultimately it dropping it to help with PCB layout.
    Allowing for a smaller loop area and reduced differential spacing.
2023-04-12 (sch) remove stability cap in ADC driver
2023-04-12 (sch) add back input comp cap
2023-04-12 (sch) fix diff naming
2023-04-12 (sch) change to ampenol conn
2023-04-12 (pcb) continue work
2023-04-12 (pcb) update board specs to ICAPE
2023-04-12 (sch) add SDIO bus spec
2023-04-12 (sch) change to 4-pin sens. conn.
2023-04-12 (sch) replace GNDA with GND
2023-04-12 (sch) assign footprint
2023-04-12 (sch) annotate PLL net
2023-04-12 (pcb) ADC layout
2023-04-12 (pcb) set trace clearances
2023-04-13 (sch) add alt part for THS4551
2023-04-13 (sch) annotate net
2023-04-13 (sch) add power test points
2023-04-13 (sch) change THS4551 from RUN to RGT
2023-04-13 (pcb) initial layout with new package
2023-04-13 change 10u cap from 0805 to 0402
2023-04-13 replace passives with 0402
2023-04-13 (pcb) implement THS4551 ref layout
2023-04-13 (sch) add comment on THS4551 pcb layout
2023-04-13 (pcb) update netclass
2023-04-14 (sch) change from handsoldering footprint to normal
2023-04-14 (sch) add VCAP net label
2023-04-14 (pcb) duplicate AFE layout
2023-04-14 (pcb) add input filter
2023-04-14 (sch) fix SAI pinout
2023-04-14 (pcb) new adc layout
2023-04-14 (pcb) tune netclasses traces
2023-04-14 (pcb) change clk netlist
2023-04-14 (sch) label pll net
2023-04-14 (pcb) improve ADC layout
2023-04-17 (sch) fix ADC pwr pins
2023-04-17 (sch) update TLV333 footprint
2023-04-17 (sch) fix BQ25125 3D model
2023-04-17 (libs) add VQFN 3d model
2023-04-17 (pcb) round off ADC layout
2023-04-17 (pcb) route ADC PLL and clock
2023-04-17 (pcb) rough layout remainder of board
2023-04-17 (sch) expose VCC on analogue connector
2023-04-17 (pcb) layout SDIO
2023-04-17 (libs) update microSD card footprint
2023-04-17 (pcb) PWR routing
2023-04-18 (sch) add neopixel placeholder
2023-04-18 (pcb) route low priority digital
2023-04-18 (pcb) change to new ICAPE stackup and reroute controlled imp.
2023-04-18 (pcb) imporve trace spacing on conn.
2023-04-18 (sch) change GNSS connector, swap RX/TX
2023-04-18 (pcb) improve SDIO routing
2023-04-18 (pcb) update clearances
2023-04-18 (pcb) improve connector routing
2023-04-19 (sch) swap LORA_INT & SD_CD pins
2023-04-19 (pcb) route buttons
2023-04-19 (pcb) route SRAM & USR LEDs
2023-04-19 (pcb) route power control sec
2023-04-19 (pcb) update min. hole drill size
2023-04-19 (pcb) route SWD conn
2023-04-19 (sch) DNP VCP LED Res.
2023-04-19 (pcb) length match high speed signal
2023-04-19 (pcb) route power
2023-04-19 (pcb) reduce edge clearance
2023-04-19 (pcb) add thicker traces
2023-04-19 (pcb) route VCC to audio conn.
2023-04-20 (pcb) add GND copper pours
2023-04-20 (pcb) finish up VCC routing
2023-04-20 (hk) clean up pcb
2023-04-20 (sch) add tantulum cap
2023-04-20 (sch) change summing stage to recommend - remove servo
2023-04-20 (sch) annotate preamp
2023-04-20 (sch) rough layout sensorboard
2023-04-21 (pcb) add Sensorboard outline and drawings
2023-04-21 (sch) annotate summation stage
2023-04-22 (hk) remove old sensor lib
2023-04-22 (libs) add TI OPA1164
2023-04-22 (libs) fix PW0016A footprint
2023-04-22 (libs) fix footprint PW0016A
2023-04-22 (sch) change to OPA1664
2023-04-23 (pcb) initial array layout
2023-04-24 (pcb) layout summing out
2023-04-24 (pcb) sensorboard rough placement
2023-04-24 (sch) add VCM decoupling
2023-04-24 (sch) add analogue VCC load switch
2023-04-24 (pcb) initial load switch layout
2023-04-24 (pcb) route load switch
2023-04-24 (pcb) remove reference designators from silkscreen
2023-04-24 (sch) fix diff to single-end conn.
2023-04-24 (pcb) add buffer to analogue netclass
2023-04-24 (pcb) rough layout sensorboard
2023-04-25 (pcb) finalise sensorboard layout
2023-04-25 (pcb) route sensor conn
2023-04-25 (pcb) route PWR on sensboard
2023-04-25 (pcb) change to power plane for sensboard
2023-04-25 (pcb) finalise sens. board
2023-04-25 (sch) clean up comments
2023-04-26 (pcb) GNSS GND via stiching
2023-04-26 (pcb) route BATT_CHG signal
2023-04-26 (pcb) ground load switch
2023-04-26 (pcb) via stitch main board
2023-04-26 (pcb) finalise GNSS board
2023-04-26 (pcb) via stitch sensor board
2023-04-27 export gerbers
2023-05-01 (pcb) start DRC process
2023-05-01 (pcb) DRC check point
2023-05-01 (sch) fix SDIO_CLK net label
2023-05-01 (pcb) add silkscreen/tattoo
2023-05-01 (prod) export gerbers
2023-05-01 (prod) update clearances
2023-05-01 (libs) update footprint
2023-05-02 (panel) update main_board config
2023-05-02 (panel) add fabrications panel tabs to mainboard
2023-05-02 (hk) move panel config to own folder
2023-05-02 (panel) export main board panel
2023-05-02 (panel) place panel fab tabs for other boards
2023-05-02 (pcb) add sensorboard silkscreen
2023-05-08 (sch) run DRC
2023-05-08 (pcb) finish silkscreen
2023-05-08 (sch) ERC exclude VSSA MCu conn
2023-05-08 (pcb) reroute PWR sensorboard
2023-05-08 (pcb) route 50&90Ohm on Trax STD stackup
2023-05-08 (proj) update stack up
2023-05-08 (pcb) fix DRC
2023-05-08 (pcb) increase edge clearance for tabs
2023-05-08 (pcb) route SAI on 50Ohm
2023-05-08 (pcb) add teardrops
2023-05-08 (panel) create prototype with all three boards
2023-05-08 (panel) add kikit config
2023-05-08 (hk) check in board backups
2023-05-08 (panel) correct origin & move to new loc.
2023-05-08 (repo) remove old panels
2023-05-08 (panel) export proto panel gerbers
2023-05-08 (repo) move single board gerbers to own dir
2023-05-08 (sch) consoldate BOM
2023-05-08 (sch) fix connector naming
2023-05-09 (sch) change 10n single-end cap to NG0
2023-05-09 (pcb) fix cap footprint & reroute
2023-05-09 (sch) remove batt override
2023-05-09 (sch) add missing "not connected"
2023-05-09 (pcb) change ERC to warn
2023-05-09 (pcb) remove ERC markers
2023-05-09 (panel) correct panel with new board
2023-05-09 (panel) export new gerber files
2023-05-09 (pcb) include DRC excl. (unsure?)
2023-05-10 (repo) do not ignore BOM files
2023-05-10 (bom) generate ibom
2023-05-10 (bom) export csv
2023-05-10 (sch) exclude mounting holes & JP from BOM
2023-05-10 (sch) DNP wire assembly
2023-05-10 (bom) export current
2023-05-10 (sch) fix BTN part number
2023-05-10 (sch) export BOM
2023-05-15 (bom) add alt part number for neopixel
2023-05-15 (pcb) clean up fab layer for hand assembly
2023-05-26 (fab) add impedance control requirements
2023-05-26 (fab) generate gerbers
2023-07-04 (pcb) update compass for manufacturing
2023-07-05 (pcb) finalise changes from fab
2023-07-05 (fab) repanelise boards
2023-07-06 (cad) update case drill work order
2023-07-27 (conf) add step output
2023-07-27 (fix) mic footprint
2023-07-27 (pcb) reduce mousbites and problamatic mousebites
2023-08-07 (fix) component MPN 0603/0402
2023-08-07 (hk) structure FAB layer for assembly
2023-09-06 chore(pinout): update IOC
2023-09-08 (pcb): fix boot selec & organise sch
2023-09-08 bc(sch): change LEDs to push-pull
2023-09-08 chore(sch): add application note to boot modes
2023-09-08 fix(sch): charge modes enable spec
2023-09-08 feat(sch): add BATT pull down to prevent rail floating
2023-09-08 docs(sch): clarify "system off"
2023-09-08 feat(pcb): add add. ON text and correct BATT off
2023-09-08 fix(pcb): add PWR and CHRG LED text
2023-09-08 fix(pcb): rearange usb shield protection
2023-09-08 feat(pcb): add SKU silkscreen
2023-09-08 fix(pcb): centre LIPO text
2023-09-08 feat(pcb): add PTH to JST connector
2023-09-08 fix(sch): change CHG_EN1 to 10k pull-up
2023-09-08 fix(sch): change PWR LEDs to 10k R
2023-09-08 fix(sch): add additional pullups for TS
2023-09-08 docs(sch): add TODOs
2023-09-08 style(sch): resize sensor block
2023-09-08 wip(sch): swap LED and conn_NSS pins
2025-12-04 chore: check in backups
2025-12-04 chore: update todos
2025-12-08 chore: update project revision
2025-12-08 docs: add comment on battery babysitter
2025-12-08 feat: redesign power switch
2025-12-09 feat: add power override jumper
2025-12-09 fix: switch polarity
2025-12-09 feat: update routing
2025-12-11 libs: update jst footprint
    include screw posts
2025-12-11 feat: final changes to pcb
2025-12-11 deps: update footprint libs
2025-12-11 style: adjust rev spacing
2025-12-11 chore: remove mask excl for mic
